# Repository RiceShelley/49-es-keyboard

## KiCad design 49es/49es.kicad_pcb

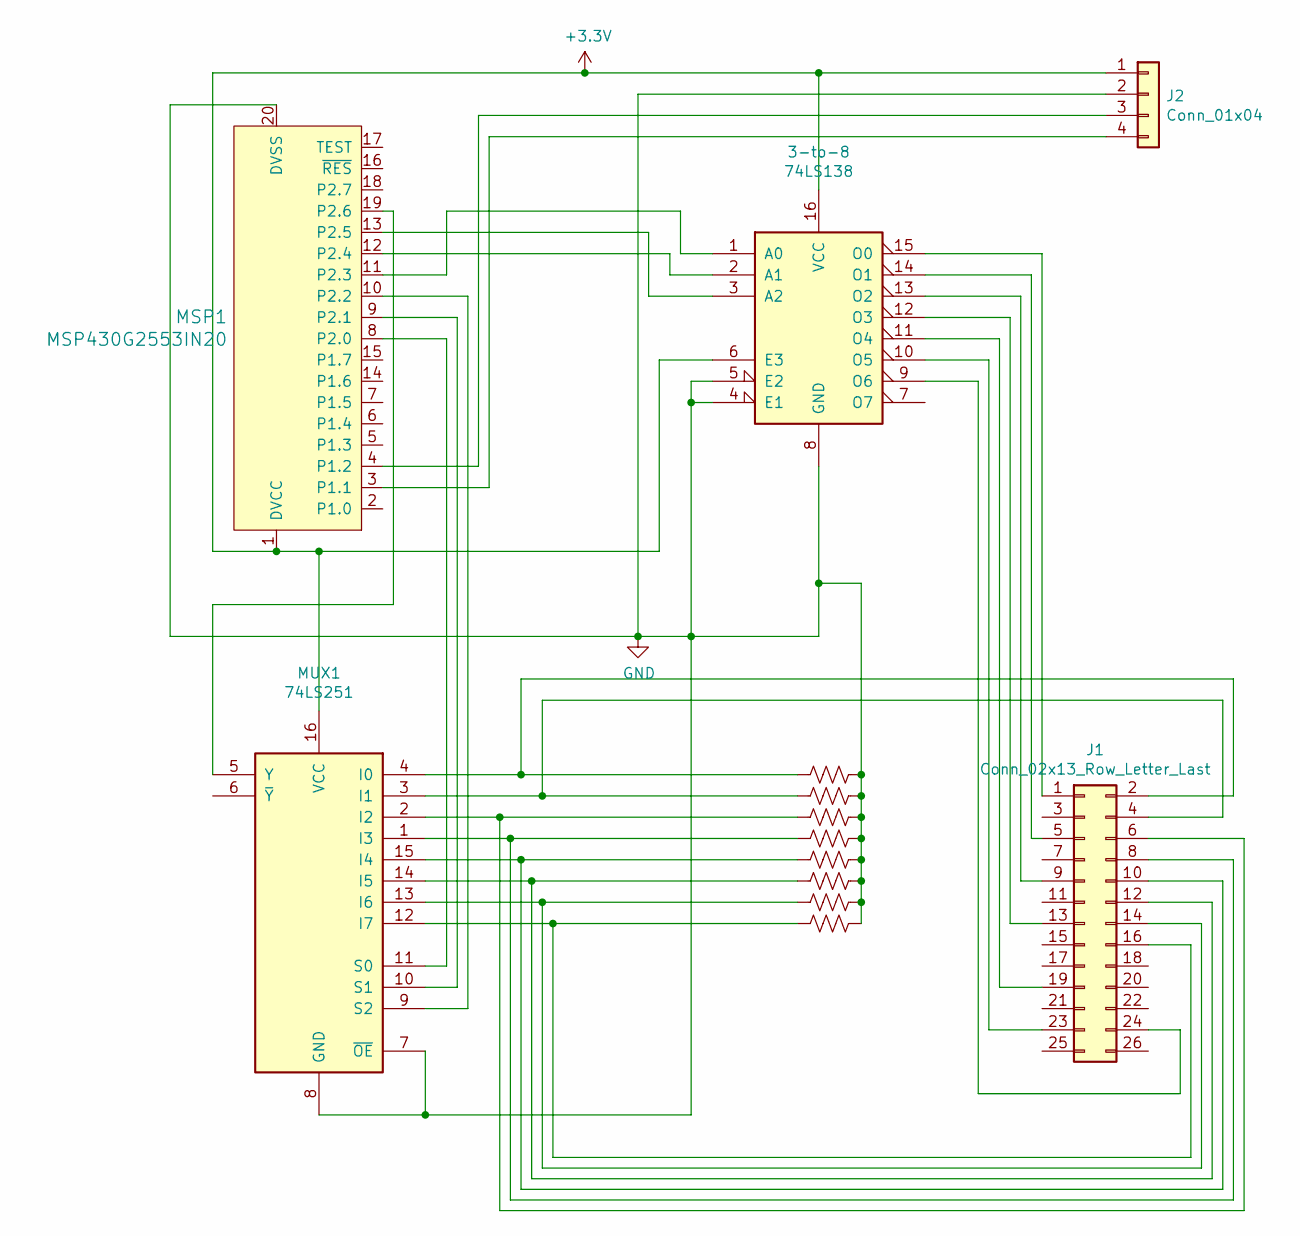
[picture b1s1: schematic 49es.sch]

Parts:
3-to-8: 74LS138; DIP-16_W7.62mm_LongPads
J1: Conn_02x13_Row_Letter_Last; IDC-Header_2x13_P2.54mm_Vertical
J2: Conn_01x04; PinHeader_1x04_P2.54mm_Vertical
MSP1: MSP430G2553IN20; DIP-20_W7.62mm_Socket_LongPads; MPN MSP430G2553IN20; Digi-Key_PN 296-28429-5-ND
MUX1: 74LS251; DIP-16_W7.62mm_LongPads
R1, R2, R3, R4, R5, R6, R7, R8: R_US; R_Axial_DIN0204_L3.6mm_D1.6mm_P7.62mm_Horizontal

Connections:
+3V3: 3-to-8.6 (E3), 3-to-8.16 (VCC), J2.1, MSP1.1 (DVCC), MUX1.16 (VCC); also elsewhere on the board
GND: 3-to-8.4 (E1), 3-to-8.5 (E2), 3-to-8.8 (GND), J2.2, MSP1.20 (DVSS), MUX1.7 (~OE), MUX1.8 (GND), R1.1, R2.1, R3.1, R4.1, R5.1, R6.1, R7.1, R8.1; also elsewhere on the board
unnamed: 3-to-8.1 (A0), MSP1.11 (P2.3)
unnamed: 3-to-8.2 (A1), MSP1.12 (P2.4)
unnamed: 3-to-8.3 (A2), MSP1.13 (P2.5)
unnamed: 3-to-8.9 (O6), J1.24
unnamed: 3-to-8.10 (O5), J1.23
unnamed: 3-to-8.11 (O4), J1.19
unnamed: 3-to-8.12 (O3), J1.13
unnamed: 3-to-8.13 (O2), J1.9
unnamed: 3-to-8.14 (O1), J1.5
unnamed: 3-to-8.15 (O0), J1.1
unnamed 13: J1.2, MUX1.4 (I0), R1.2; also elsewhere on the board
unnamed 15: J1.4, MUX1.3 (I1), R2.2; also elsewhere on the board
unnamed 16: J1.6, MUX1.2 (I2), R3.2; also elsewhere on the board
unnamed 18: J1.8, MUX1.1 (I3), R4.2; also elsewhere on the board
unnamed 19: J1.10, MUX1.15 (I4), R5.2; also elsewhere on the board
unnamed 21: J1.12, MUX1.14 (I5), R6.2; also elsewhere on the board
unnamed 22: J1.14, MUX1.13 (I6), R7.2; also elsewhere on the board
unnamed 24: J1.16, MUX1.12 (I7), R8.2; also elsewhere on the board
unnamed: J2.3, MSP1.4 (P1.2)
unnamed: J2.4, MSP1.3 (P1.1)
unnamed 38: MSP1.8 (P2.0), MUX1.11 (S0); also elsewhere on the board
unnamed 39: MSP1.9 (P2.1), MUX1.10 (S1); also elsewhere on the board
unnamed 40: MSP1.10 (P2.2), MUX1.9 (S2); also elsewhere on the board
unnamed 46: MSP1.19 (P2.6), MUX1.5 (Y); also elsewhere on the board

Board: 2 copper layers, 13 parts (0 on the bottom side), 26 nets, no tracks yet.

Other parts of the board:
MUX: 74LS251; DIP-16_W7.62mm_LongPads

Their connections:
+3V3: MUX.16; also elsewhere on the board
GND: MUX.7, MUX.8; also elsewhere on the board
unnamed 13: MUX.4; also elsewhere on the board
unnamed 15: MUX.3; also elsewhere on the board
unnamed 16: MUX.2; also elsewhere on the board
unnamed 18: MUX.1; also elsewhere on the board
unnamed 19: MUX.15; also elsewhere on the board
unnamed 21: MUX.14; also elsewhere on the board
unnamed 22: MUX.13; also elsewhere on the board
unnamed 24: MUX.12; also elsewhere on the board
unnamed 38: MUX.11; also elsewhere on the board
unnamed 39: MUX.10; also elsewhere on the board
unnamed 40: MUX.9; also elsewhere on the board
unnamed 46: MUX.5; also elsewhere on the board

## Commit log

2019-02-06 welp
2019-02-06 fixes
